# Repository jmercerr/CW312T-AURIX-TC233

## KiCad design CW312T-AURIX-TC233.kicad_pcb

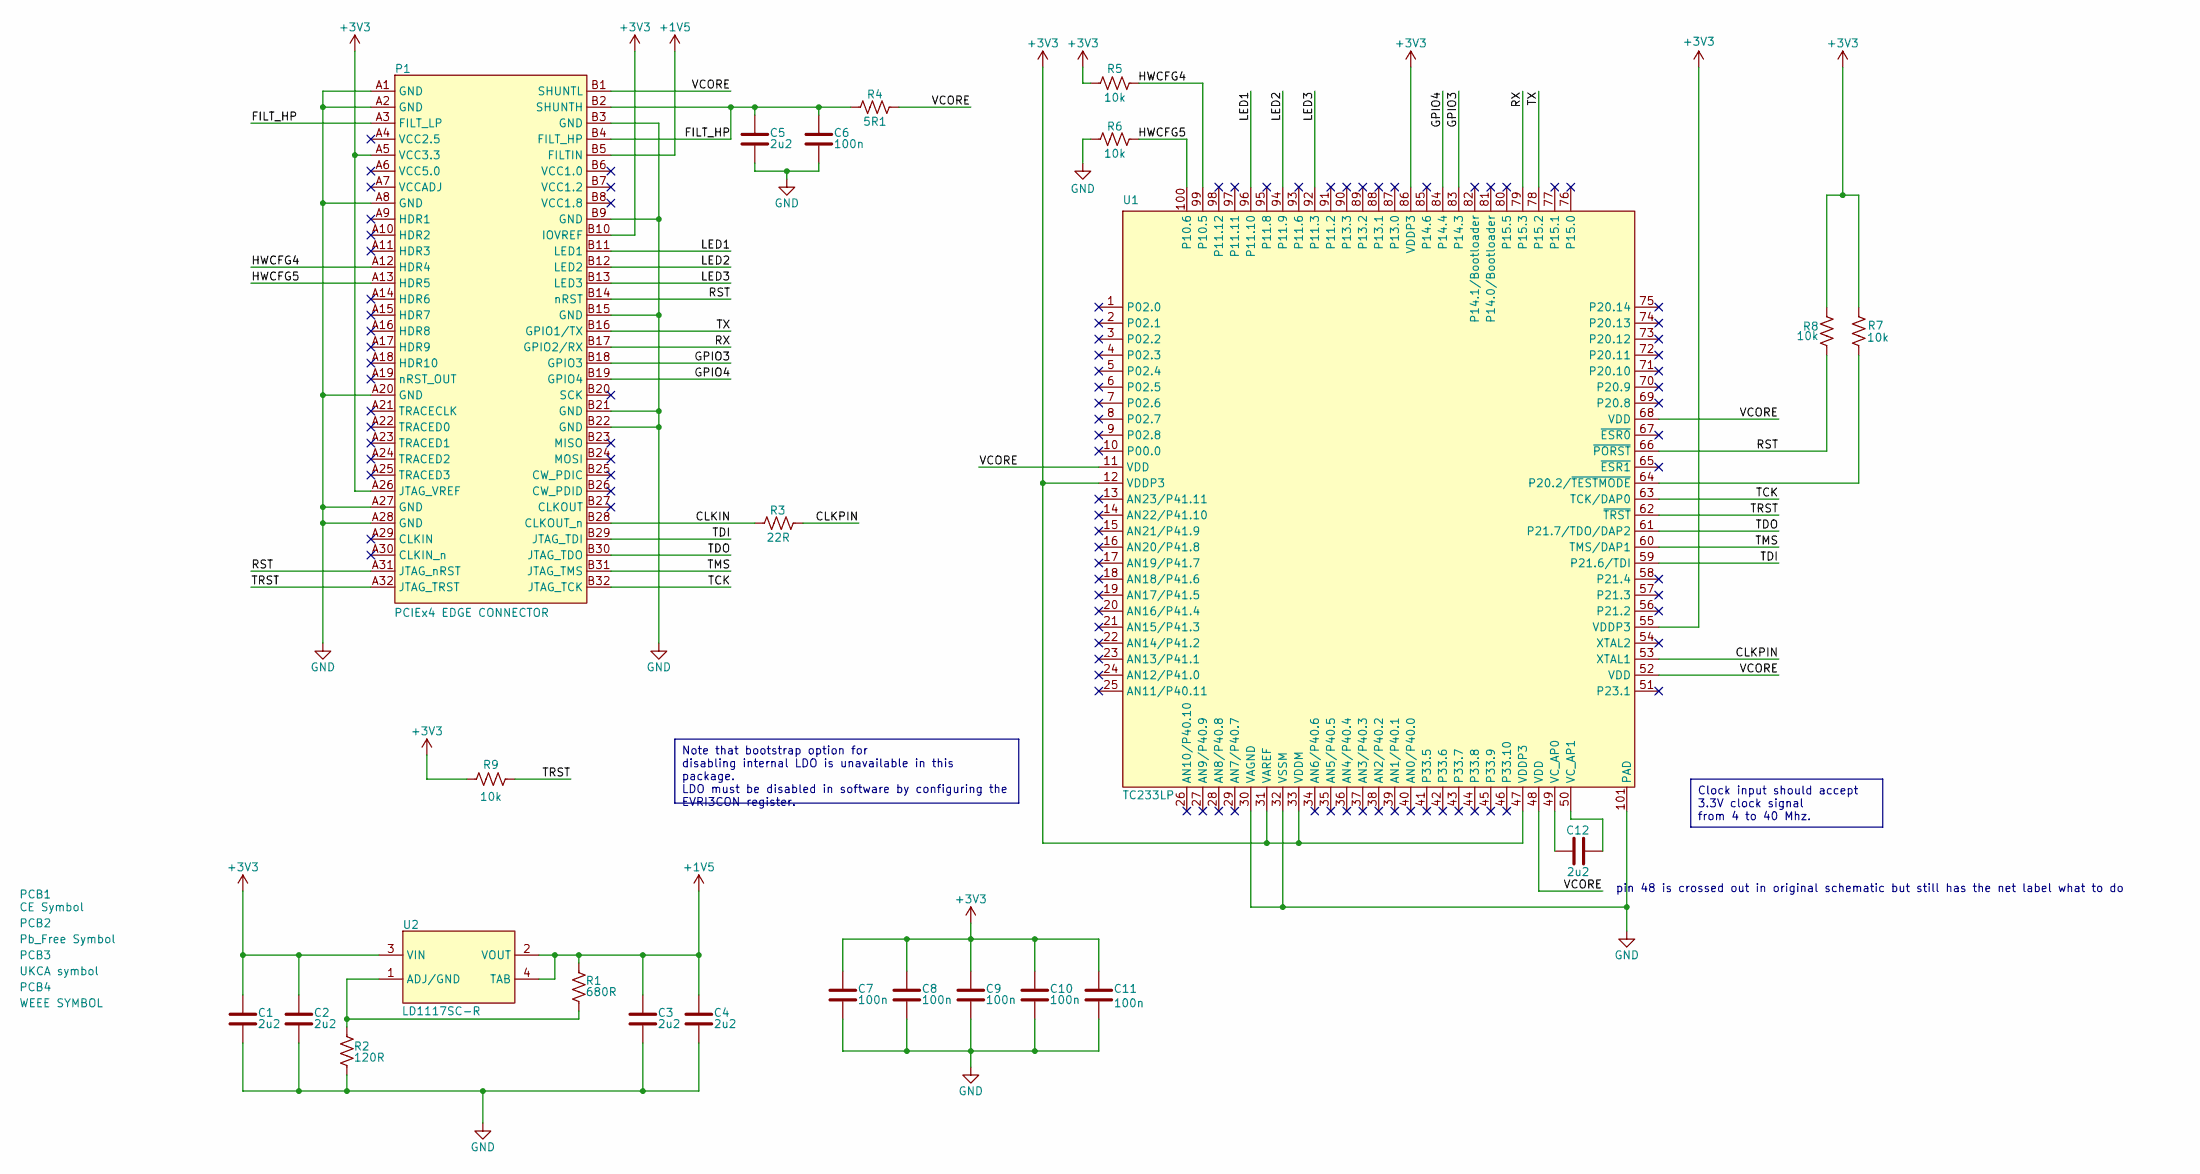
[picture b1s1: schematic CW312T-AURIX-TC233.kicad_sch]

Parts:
C1, C2, C3, C4, C5, C12: CAP_2u2_10V_0603; C_0603_1608Metric; Manufacturer Part Number CC0603KPX7R6BB225
C6, C7, C8, C9, C10, C11: CAP_100n_50V_0603; C_0603_1608Metric; Manufacturer Part Number CC0603KRX7R9BB104
P1: PCIEx4 EDGE CONNECTOR; CW312_Template
PCB1: CE Symbol; CE-Logo_8.5x6mm_SilkScreen
PCB2: Pb_Free Symbol; Pb_Free_8.0x8.0mm_SilkScreen
PCB3: UKCA symbol; UKCA-Logo_8x8mm_SilkScreen
PCB4: WEEE SYMBOL; WEEE-Logo_5.6x8mm_SilkScreen
R1: RES_680R_0603; R_0603_1608Metric; Manufacturer Part Number RC0603FR-07680RL
R2: RES_120R_0603; R_0603_1608Metric; Manufacturer Part Number RC0603FR-07120RL
R3: RES_22R_0603; R_0603_1608Metric; Manufacturer Part Number RC0603FR-0722RL
R4: RES_5R1_0603; R_0603_1608Metric; Manufacturer Part Number RC0603FR-075R1L
R5, R6, R7, R8, R9: RES_10k_0603; R_0603_1608Metric; Manufacturer Part Number RC0603FR-0710KL
U1: TC233LP32F200NACKXUMA1; TQFP-100-1EP_14x14mm_P0.5mm_EP5x5mm; Manufacturer Part Number TC233LP32F200NACKXUMA1
U2: LD1117SC-R; SOT-223; Manufacturer Part Number LD1117SC-R

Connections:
+1V5: C3.2, C4.2, P1.B5 (FILTIN), R1.2, U2.2 (VOUT), U2.4 (TAB)
+3V3: C1.2, C2.2, C7.2, C8.2, C9.2, C10.2, C11.2, P1.A5 (VCC3.3), P1.A26 (JTAG_VREF), P1.B10 (IOVREF), R5.1, R7.2, R8.2, R9.1, U1.12 (VDDP3), U1.31 (VAREF), U1.33 (VDDM), U1.47 (VDDP3), U1.55 (VDDP3), U1.86 (VDDP3), U2.3 (VIN)
/CLKIN: P1.B28 (CLKOUT_n), R3.2
/CLKPIN: R3.1, U1.53 (XTAL1)
/FILT_HP: C5.2, C6.2, P1.A3 (FILT_LP), P1.B2 (SHUNTH), P1.B4 (FILT_HP), R4.1
/GPIO3: P1.B18 (GPIO3), U1.83 (P14.3)
/GPIO4: P1.B19 (GPIO4), U1.84 (P14.4)
/HWCFG4: P1.A12 (HDR4), R5.2, U1.99 (P10.5)
/HWCFG5: P1.A13 (HDR5), R6.2, U1.100 (P10.6)
/LED1: P1.B11 (LED1), U1.96 (P11.10)
/LED2: P1.B12 (LED2), U1.94 (P11.9)
/LED3: P1.B13 (LED3), U1.92 (P11.3)
/RST: P1.A31 (JTAG_nRST), P1.B14 (nRST), R8.1, U1.66 (~PORST)
/RX: P1.B17 (GPIO2/RX), U1.79 (P15.3)
/TCK: P1.B32 (JTAG_TCK), U1.63 (TCK/DAP0)
/TDI: P1.B29 (JTAG_TDI), U1.59 (P21.6/TDI)
/TDO: P1.B30 (JTAG_TDO), U1.61 (P21.7/TDO/DAP2)
/TMS: P1.B31 (JTAG_TMS), U1.60 (TMS/DAP1)
/TRST: P1.A32 (JTAG_TRST), R9.2, U1.62 (~TRST)
/TX: P1.B16 (GPIO1/TX), U1.78 (P15.2)
/VCORE: P1.B1 (SHUNTL), R4.2, U1.11 (VDD), U1.48 (VDD), U1.52 (VDD), U1.68 (VDD)
GND: C1.1, C2.1, C3.1, C4.1, C5.1, C6.1, C7.1, C8.1, C9.1, C10.1, C11.1, P1.A1 (GND), P1.A2 (GND), P1.A8 (GND), P1.A20 (GND), P1.A27 (GND), P1.A28 (GND), P1.B3 (GND), P1.B9 (GND), P1.B15 (GND), P1.B21 (GND), P1.B22 (GND), R2.1, R6.1, U1.30 (VAGND), U1.32 (VSSM), U1.101 (PAD)
unnamed: R7.1, U1.64 (P20.2/~TESTMODE)
unnamed: C12.1, U1.49 (VC_AP0)
unnamed: C12.2, U1.50 (VC_AP1)
unnamed: R1.1, R2.2, U2.1 (ADJ/GND)

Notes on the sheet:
Clock input should accept 3.3V clock signal from 4 to 40 Mhz.
Note that bootstrap option for disabling internal LDO is unavailable in this package. LDO must be disabled in software by configuring the EVRI3CON register.
pin 48 is crossed out in original schematic but still has the net label what to do

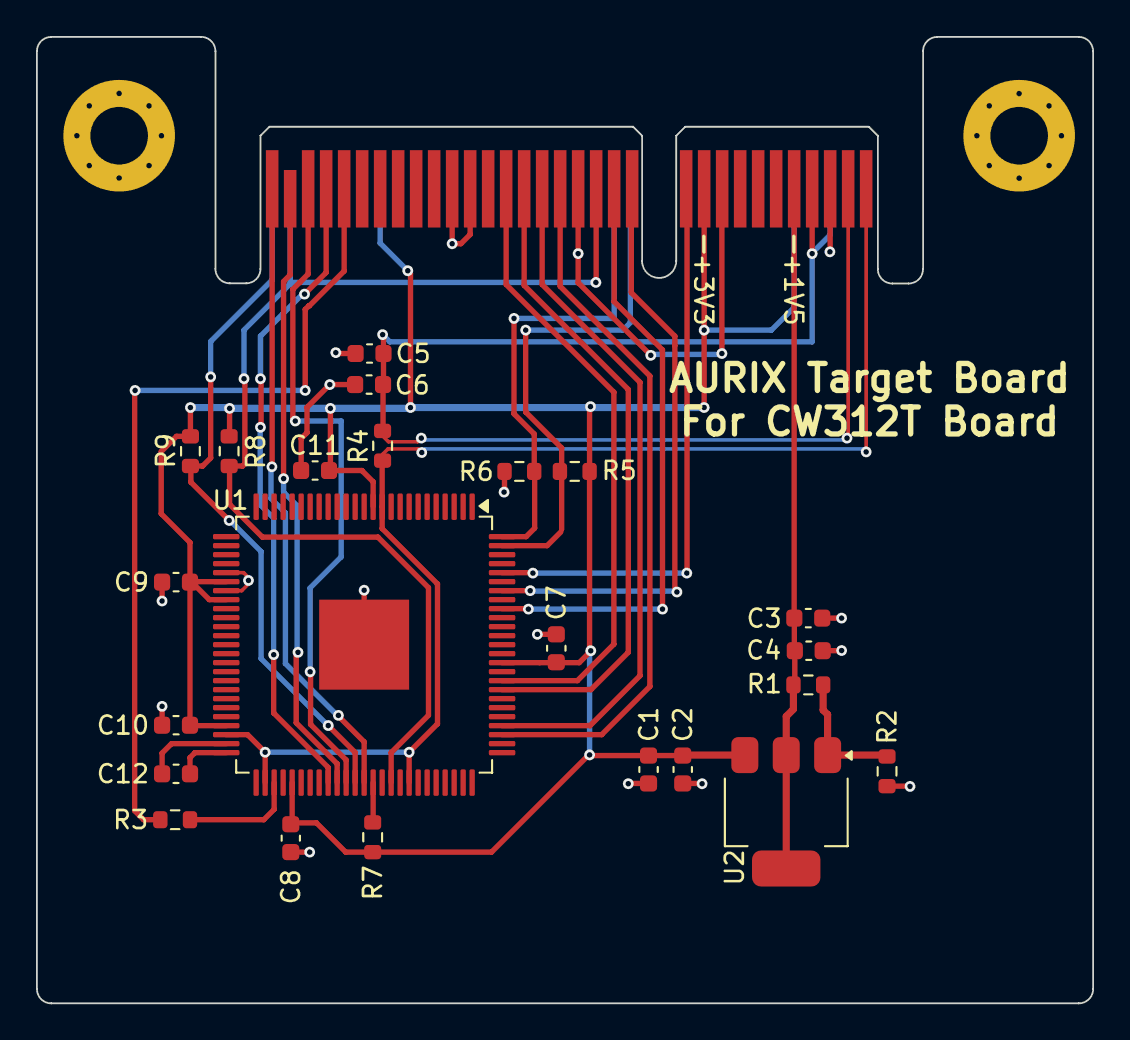
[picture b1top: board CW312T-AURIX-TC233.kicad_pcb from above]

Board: 2 copper layers, 58.7 x 53.7 mm, 28 parts (0 on the bottom side), 26 nets.

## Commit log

2024-11-28 first draft - ready for review
2024-12-04 updated schematic, pcb and production files - ready for review
2024-12-04 updated silkscreen and production files
2024-12-20 updated schematic and pcb after library reorganization
